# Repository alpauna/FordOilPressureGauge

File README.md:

# FordOilPressureGauge
Add actual oil pressure to Ford and allows for dash light to still work via ATTiny uCPU

## Hardware
Uses a board that I developed and all is in schematics folder.

## Software
Arduino based ATTiny85 for original revision.
New revision is ATTiny1624 and it will add buttons so that some items can be adjusted

## Blog
Check out the progress of this in my [alshowto.com](https://alshowto.com) page. Also, you can check out the tag related to the truck that 
inspired this project: [99 f150](https://alshowto.com/tag/99-f150/).

Finally, if just insterested in this project check out the blog on it. [Add an Actual Oil Pressure Gauge](https://alshowto.com/99-f150-add-an-actual-oil-pressure-gauge/)

## Latest development

## Testing
Testing the drive capability of the n-mosfet. However for the truck it is simply switching the dash oil circuit to ground so it should be very low current.

## Dash circuit

As seen above, I think this circuit is grounded out to turn the oil light on so the code will drive pin 17 high to turn on the MOSFET and this will then send that dash circuit Pin 6 on I/O connector to ground. The code is set to do this if the pressure drops below 10 PSI. I think the original circuit did this at 7 psi. 

I will provide more specifics once I fully test this on my trucks. This may be exactly backward and it should be grounded when the light is off and basically open to have the light on. Running on my truck will verify this fact. That will happen sometime next month with my prototype board running the ATTiny85.

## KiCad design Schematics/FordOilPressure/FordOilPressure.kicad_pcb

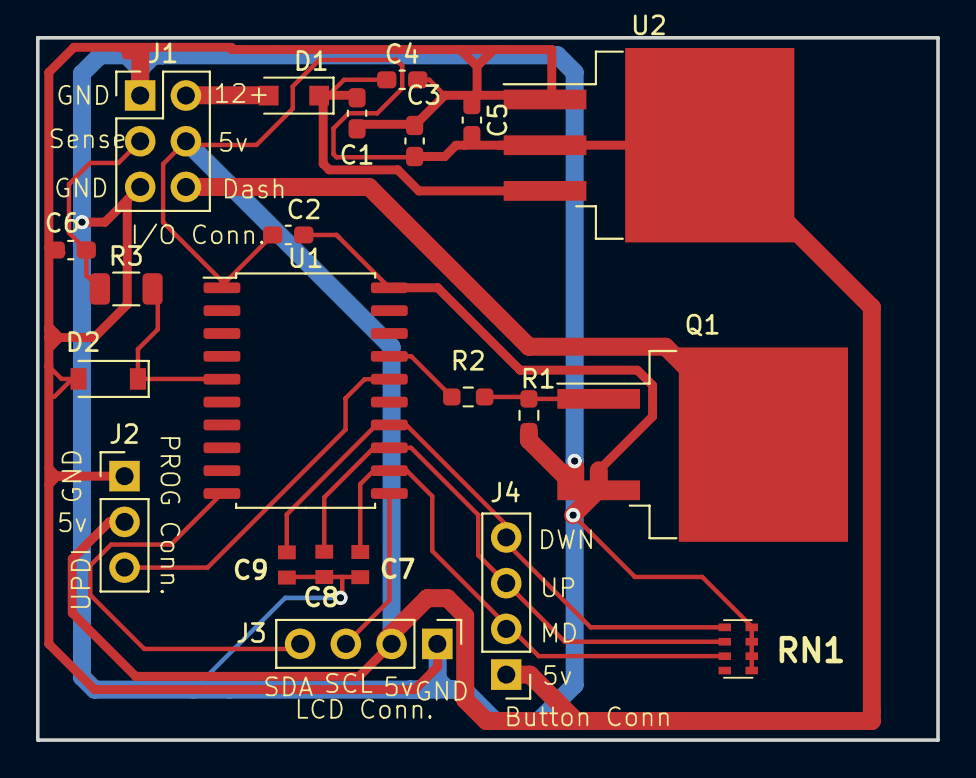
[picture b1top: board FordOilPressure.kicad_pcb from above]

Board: 2 copper layers, 50.0 x 39.0 mm, 22 parts (0 on the bottom side), 15 nets.

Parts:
C1, C5: 10uF; C_0603_1608Metric_Pad1.08x0.95mm_HandSolder
C2, C4: .1uF; C_0603_1608Metric_Pad1.08x0.95mm_HandSolder
C3, C6: .33uF; C_0603_1608Metric_Pad1.08x0.95mm_HandSolder
C7, C8, C9: 0603YC105KAT2A; CAPC1608X94N
D1: 1 amp; D_SOD-123F
D2: 5.1 v; D_SOD-123
J1: I/O Connector; PinHeader_2x03_P2.54mm_Vertical
J2: UPDI; PinHeader_1x03_P2.54mm_Vertical
J3: LCD Conn; PinHeader_1x04_P2.54mm_Vertical
J4: Btn Connect; PinHeader_1x04_P2.54mm_Vertical
Q1: PHB21N06LT,118; TO-263-2
R1: 10M; R_0603_1608Metric_Pad0.98x0.95mm_HandSolder
R2: 1k; R_0603_1608Metric_Pad0.98x0.95mm_HandSolder
R3: 1k; R_1206_3216Metric
RN1: EXBV8V683JV; EXBV8V101JV
U1: ATtiny1616-S; SOIC-20W_7.5x12.8mm_P1.27mm
U2: LM1085-5.0; TO-263-3_TabPin2

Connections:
GND: C1.1, C2.2, C3.2, C4.2, C5.1, C6.1, C7.1, C8.1, C9.1, D2.2 (A), J1.1, J1.5, J2.1, J3.1, Q1.3 (S), R1.2, RN1.1, RN1.2, RN1.3, RN1.4, U1.20 (GND), U2.1 (GND)
unnamed: C2.1, C3.1, C5.2, J1.4, J2.2, J3.2, J4.1, U1.1 (VCC), U2.2 (VO)
unnamed: D1.2 (A), J1.2
unnamed: D2.1 (K), R3.2, U1.5 (PA7)
unnamed: C6.2, J1.3, R3.1
unnamed: J1.6, Q1.2 (D)
unnamed: J2.3, U1.16 (~RESET/PA0)
unnamed: J3.3, U1.11 (PB0)
unnamed: J3.4, U1.10 (PB1)
unnamed: Q1.1 (G), R1.1, R2.2
unnamed: R2.1, U1.17 (PA1)
unnamed: C7.2, J4.2, RN1.7, U1.12 (PC0)
unnamed: C8.2, J4.3, RN1.6, U1.13 (PC1)
unnamed: C9.2, J4.4, RN1.5, U1.14 (PC2)
unnamed: C1.2, C4.1, D1.1 (K), U2.3 (VI)

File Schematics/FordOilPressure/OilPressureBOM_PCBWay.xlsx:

|  |  | xxxx xxxx xxxxx xxPCS BOM (Sample Bill of Materials)
Item # | *Designator | *Qty | Manufacturer | *Mfg Part # | Description / Value | *Package/Footprint | Type | Your Instructions / Notes
1 | C1,C3 | 2 | Murata Electronics | GRM188R6YA106MA73D | 35V 10uF ±20% 0603 Multilayer Ceramic Capacitors | 0603 | SMD
2 | C2 | 1 | Knowles | 0603Y0250104KET | 25V 100nF ±10% 0603 Multilayer Ceramic Capacitors | 0603 | SMD
3 | D1 | 1 | Shikues | MBR130 | 30V 470mV@1A 1A SOD-123 Schottky Barrier Diodes | SOD-123 | SMD
4 | D2 | 1 | Diodes Inc | DDZ5V1B-7 | 5uA@1.5V 17Ω Single 4.94V~5.2V 470mW Zener Diodes | SOD-123 | SMD
5 | J1 | 1 | TE Connectivity | 5-146258-3 | Connector_PinHeader_2.54mm:PinHeader_2x03_P2.54mm_Vertical | 2.54 Pin Header | thru-hole
6 | J2 | 1 | TE Connectivity | 5-146258-3 | Connector_PinHeader_2.54mm:PinHeader_2x03_P2.54mm_Vertical | 2.54 Pin Header | thru-hole
7 | J3 | 1 | Amphenol ICC | 68001-204HLF | Connector_PinHeader_2.54mm:PinHeader_1x04_P2.54mm_Vertical | 2.54 Pin Header | thru-hole
8 | Q1 | 1 | Nexperia | PHB21N06LT,118 | MOSFET 55v 19a 2v GS | SOT404 | SMD
9 | R1 | 1 | Vishay Intertech | MCT06030C1005FP500 | 100mW 10MΩ 0603 Chip Resistor | 0603 | SMD
10 | R2,R3 | 2 | BOURNS | CR0603AFX-1001ELF | 100mW 1KΩ 0603 Chip Resistor | 0603 | DNS
11 | U1 | 1 | Microchip Tech | ATTINY85-20SF | uConn 4K@x16bit -40℃~+85℃ 2.7V~5.5V AVR 1@x4ch/10bit Yes 20MHz 6 512Byte | SOIC-8 | SMD
12 | U2 | 1 | HGSEMI | LM1085S-5.0/TR | 3AFixed 5V~5V Positive 1 15V TO-263-3 Linear Voltage Regulators | TO-263-3 | SMD
Need a quick and accurante quote? Need an efficient production? Please read SMT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
Click for Instructions on How to Create a BOM

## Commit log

2022-12-31 Initial Checkin
    Initial check in of basic working oil pressure sensor .
2023-01-08 Created Readme file
2023-01-08 updated code that better zeros the pressure gauge.
    This latest code is just before I started to develop for the ATTiny 1624 to replace the ATTiny85 uCPU.
2023-01-08 Had a mis spelling that I found
2023-01-08 Started the ATTiny 1626 development
2023-01-08 Added photos and some more details.
2023-01-08 Fixed some header issues
2023-01-08 Just cleaning up as I forgot to push these to github.
    ATTiny85 codebase version prior to transitioning to ATTiny1626 version.
2023-01-08 This is the latest with ATTiny1626
2023-01-28 most complete one tested on first board v 1.0
    Added much logic and a button that can be added to reset and re-zero the gauge.
2023-01-28 Progression On ATTyiny1626
